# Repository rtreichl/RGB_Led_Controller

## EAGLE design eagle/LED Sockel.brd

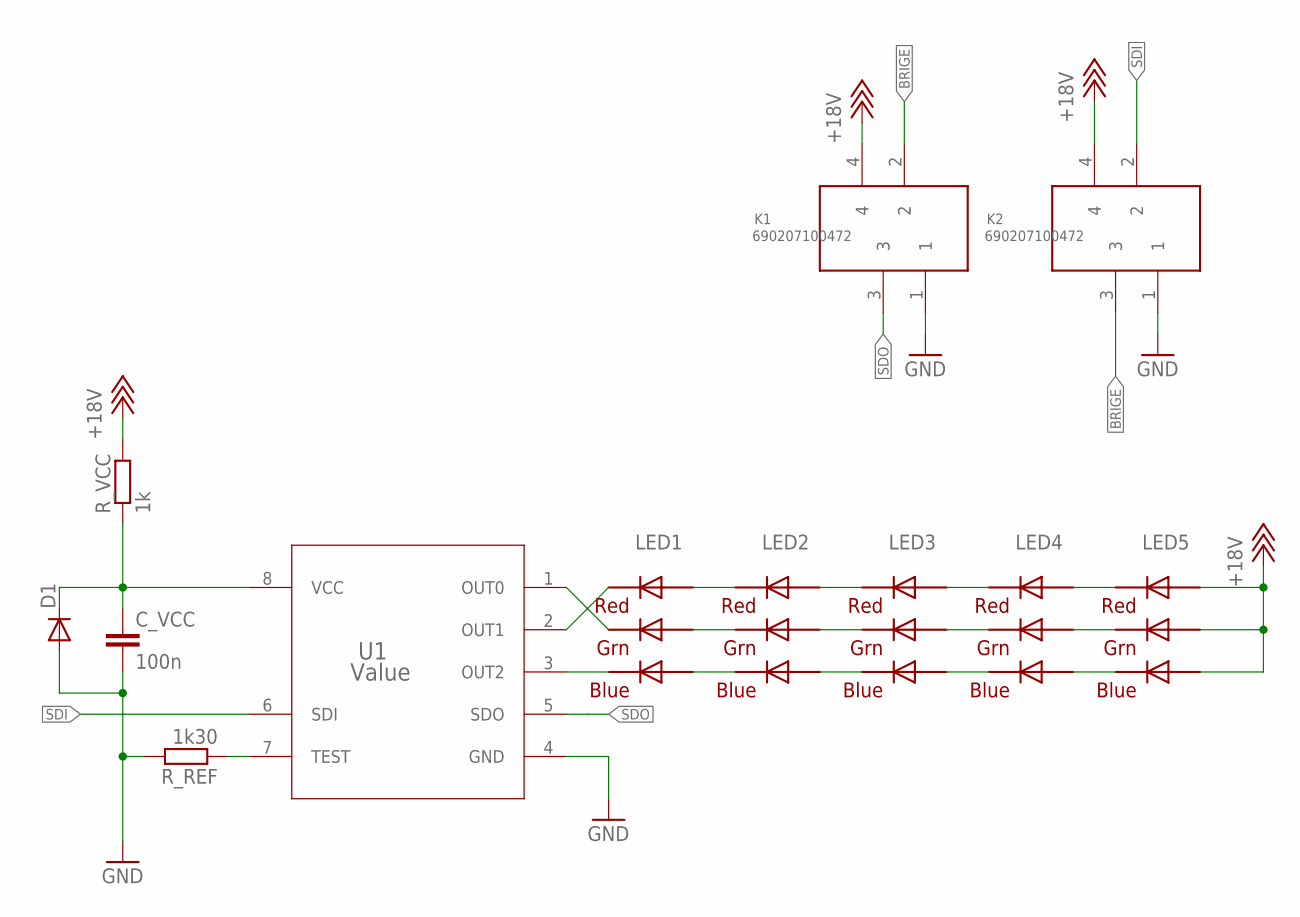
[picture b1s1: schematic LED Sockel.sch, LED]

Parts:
C_VCC: 100n; C0603
D1: DIODE-SOD523; SOD523
K1, K2: 690207100472
LED1, LED2, LED3, LED4, LED5: RGBLED5050
R_REF: 1k30; R0603
R_VCC: 1k; R0805
U1: Value; D0008A_N

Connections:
+18V: K1.4, K2.4, LED5.1 (GREEN_A), LED5.2 (RED_A), LED5.3 (BLUE_A), R_VCC.2
BRIGE: K1.2, K2.3
GND: C_VCC.2, D1.A, K1.1, K2.1, R_REF.2, U1.4 (GND)
unnamed: LED4.1 (GREEN_A), LED5.6 (GREEN_C)
unnamed: LED4.3 (BLUE_A), LED5.4 (BLUE_C)
unnamed: LED4.2 (RED_A), LED5.5 (RED_C)
unnamed: LED3.1 (GREEN_A), LED4.6 (GREEN_C)
unnamed: LED3.3 (BLUE_A), LED4.4 (BLUE_C)
unnamed: LED3.2 (RED_A), LED4.5 (RED_C)
unnamed: LED2.1 (GREEN_A), LED3.6 (GREEN_C)
unnamed: LED2.3 (BLUE_A), LED3.4 (BLUE_C)
unnamed: LED2.2 (RED_A), LED3.5 (RED_C)
unnamed: LED1.1 (GREEN_A), LED2.6 (GREEN_C)
unnamed: LED1.3 (BLUE_A), LED2.4 (BLUE_C)
unnamed: LED1.2 (RED_A), LED2.5 (RED_C)
unnamed: LED1.4 (BLUE_C), U1.3 (OUT2)
unnamed: LED1.6 (GREEN_C), U1.1 (OUT0)
unnamed: LED1.5 (RED_C), U1.2 (OUT1)
unnamed: C_VCC.1, D1.C, R_VCC.1, U1.8 (VCC)
unnamed: R_REF.1, U1.7 (TEST)
SDI: K2.2, U1.6 (SDI)
SDO: K1.3, U1.5 (SDO)

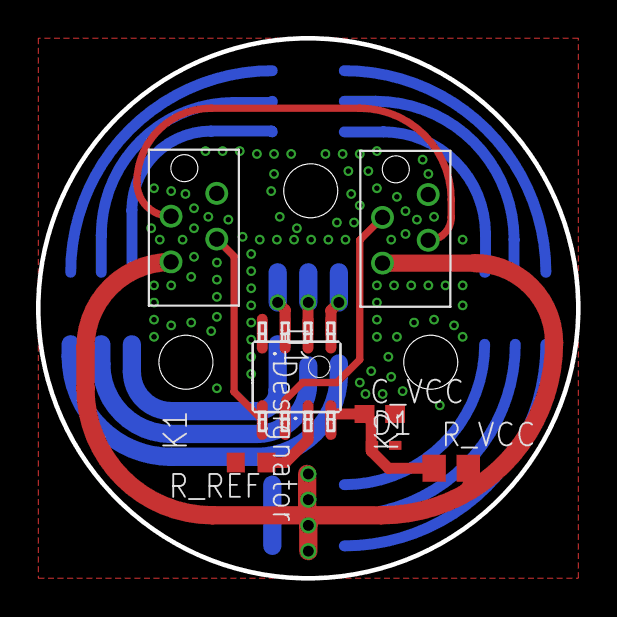
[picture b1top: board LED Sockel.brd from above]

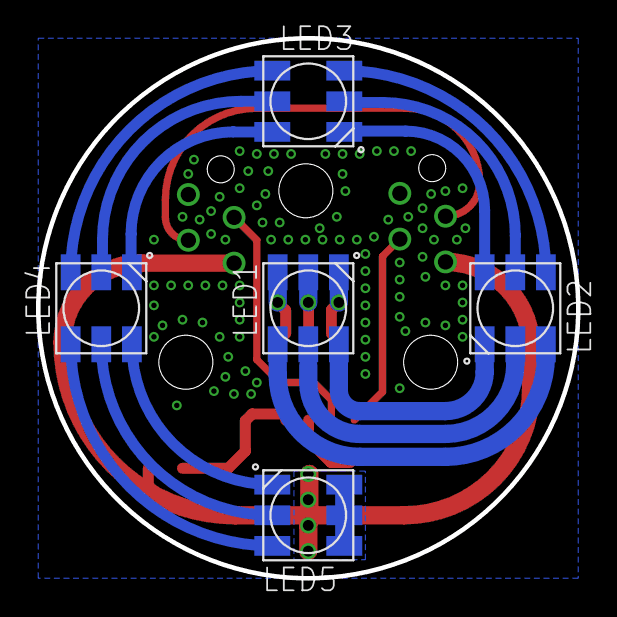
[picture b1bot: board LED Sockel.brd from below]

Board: 2 copper layers, 30.0 x 30.0 mm, 12 parts (5 on the bottom side), 22 nets.

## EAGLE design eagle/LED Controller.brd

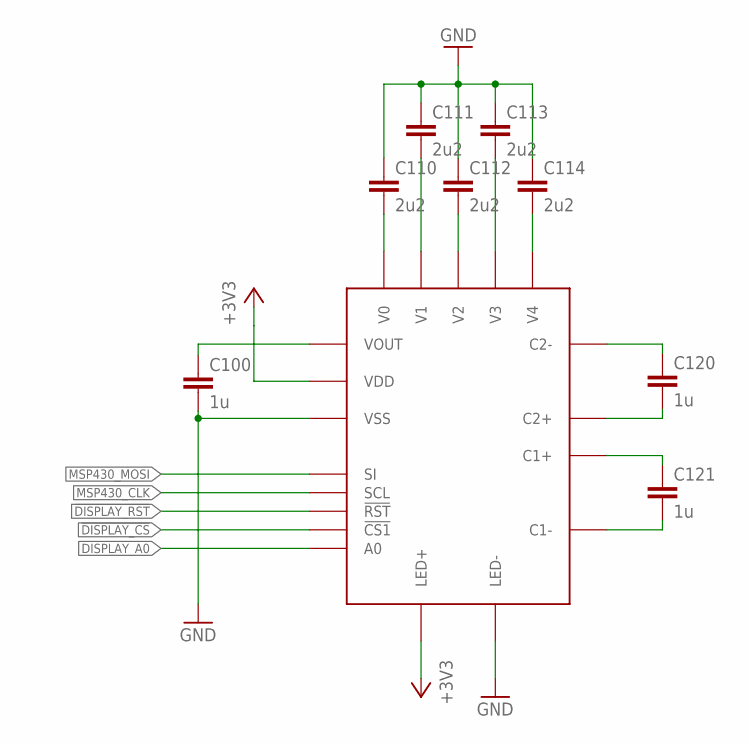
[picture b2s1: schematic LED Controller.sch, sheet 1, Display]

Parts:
C100, C120, C121: 1u; C0603
C110, C111, C112, C113, C114: 2u2; C0603
U$3: DISPLAY; NHD-C12832A1Z-NSW-BBW-3V3

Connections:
!DISPLAY_CS: U$3.P17 (!CS1); also elsewhere on the board
!DISPLAY_RST: U$3.P16 (!RST); also elsewhere on the board
+3V3: U$3.A (LED+), U$3.P12 (VDD); also elsewhere on the board
DISPLAY_A0: U$3.P15 (A0); also elsewhere on the board
GND: C100.2, C110.1, C111.1, C112.1, C113.1, C114.1, U$3.K (LED-), U$3.P11 (VSS); also elsewhere on the board
MSP430_CLK: U$3.P14 (SCL); also elsewhere on the board
MSP430_MOSI: U$3.P13 (SI); also elsewhere on the board
unnamed: C110.2, U$3.P1 (V0)
unnamed: C111.2, U$3.P2 (V1)
unnamed: C112.2, U$3.P3 (V2)
unnamed: C113.2, U$3.P4 (V3)
unnamed: C114.2, U$3.P5 (V4)
unnamed: C120.2, U$3.P7 (C2+)
unnamed: C120.1, U$3.P6 (C2-)
unnamed: C121.1, U$3.P8 (C1+)
unnamed: C121.2, U$3.P9 (C1-)
unnamed: C100.1, U$3.P10 (VOUT)

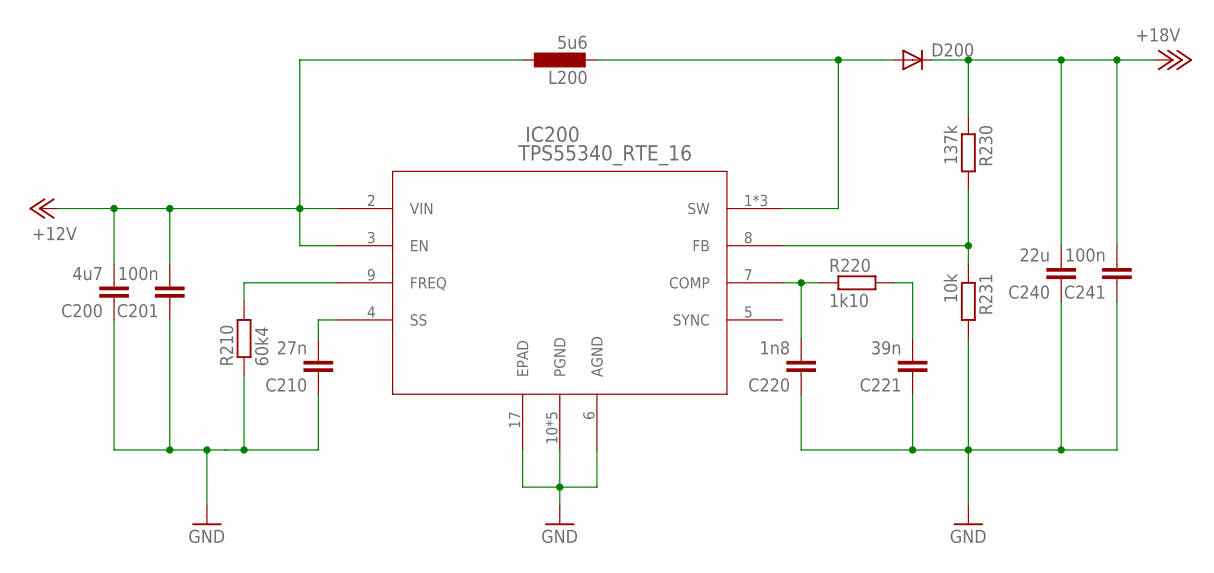
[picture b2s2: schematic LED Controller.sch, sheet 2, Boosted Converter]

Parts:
C200: 4u7; C1206
C201, C241: 100n; C1206
C210: 27n; C0603
C220: 1n8; C0603
C221: 39n; C0603
C240: 22u; C1210
D200: DIODE-SMC; SMC
IC200: TPS55340_RTE_16; RTE16
L200: 5u6; SRP5030T
R210: 60k4; R0603
R220: 1k10; R0603
R230: 137k; R0603
R231: 10k; R0603

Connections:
+12V: C200.2, C201.2, IC200.2 (VIN), IC200.3 (EN), L200.V_1 (1); also elsewhere on the board
+18V: C240.2, C241.2, D200.C, R230.1; also elsewhere on the board
GND: C200.1, C201.1, C210.1, C220.1, C221.1, C240.1, C241.1, IC200.6 (AGND), IC200.10 (PGND), IC200.11 (PGND), IC200.12 (PGND), IC200.13 (PGND), IC200.14 (PGND), IC200.17 (EPAD), R210.1, R231.2; also elsewhere on the board
unnamed: C220.2, IC200.7 (COMP), R220.1
unnamed: D200.A, IC200.1 (SW), IC200.15 (SW), IC200.16 (SW), L200.V_2 (2)
unnamed: IC200.8 (FB), R230.2, R231.1
unnamed: IC200.9 (FREQ), R210.2
unnamed: C210.2, IC200.4 (SS)
unnamed: C221.2, R220.2

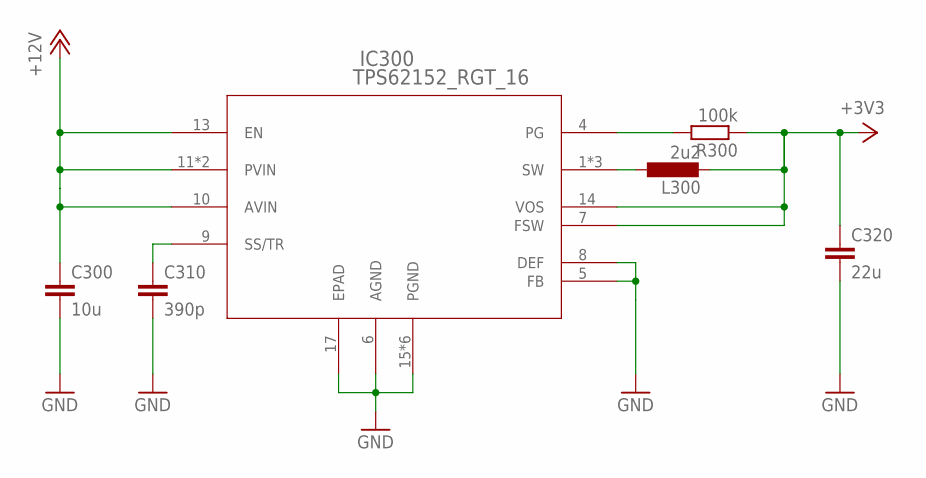
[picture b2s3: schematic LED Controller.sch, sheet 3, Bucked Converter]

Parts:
C300: 10u; C0805
C310: 390p; C0603
C320: 22u; C0805
IC300: TPS62152_RGT_16; RGT16_1P7X1P7
L300: 2u2; SDR0403
R300: 100k; R0603

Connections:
+3V3: C320.1, IC300.7 (FSW), IC300.14 (VOS), L300.V_2 (2), R300.1; also elsewhere on the board
+12V: C300.1, IC300.10 (AVIN), IC300.11 (PVIN), IC300.12 (PVIN), IC300.13 (EN); also elsewhere on the board
GND: C300.2, C310.2, C320.2, IC300.5 (FB), IC300.6 (AGND), IC300.8 (DEF), IC300.15 (PGND), IC300.16 (PGND), IC300.17 (EPAD), IC300.V (PGND), IC300.V_1 (PGND), IC300.V_2 (PGND), IC300.V_3 (PGND); also elsewhere on the board
unnamed: IC300.1 (SW), IC300.2 (SW), IC300.3 (SW), L300.V_1 (1)
unnamed: IC300.4 (PG), R300.2
unnamed: C310.1, IC300.9 (SS/TR)

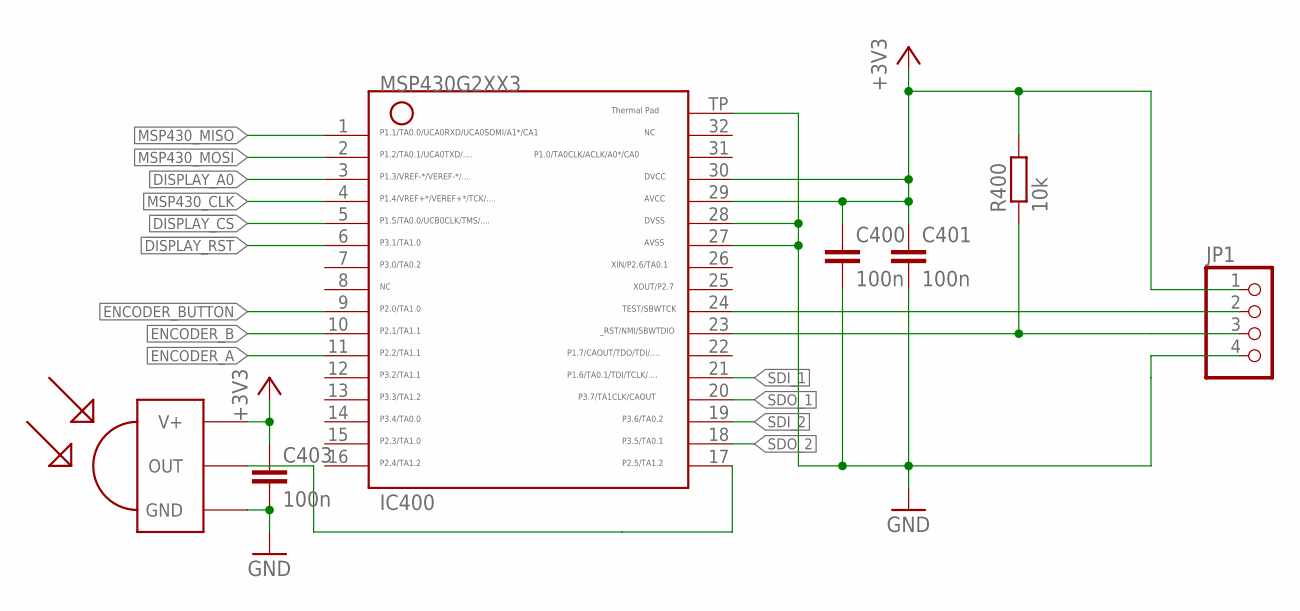
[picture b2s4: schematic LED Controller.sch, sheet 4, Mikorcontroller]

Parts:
C400, C401, C403: 100n; C0603
IC400: G2XX3---RHB32; RHB32
JP1: PINHD-1X4; 1X04
R400: 10k; R0603
U$1: TSOP1738; TSOP17XX

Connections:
!DISPLAY_CS: IC400.5; also elsewhere on the board
!DISPLAY_RST: IC400.6; also elsewhere on the board
+3V3: C400.1, C401.1, C403.1, IC400.29, IC400.30, JP1.1, R400.2, U$1.V+; also elsewhere on the board
DISPLAY_A0: IC400.3; also elsewhere on the board
ENCODER_A: IC400.11; also elsewhere on the board
ENCODER_B: IC400.10; also elsewhere on the board
ENCODER_BUTTON: IC400.9; also elsewhere on the board
GND: C400.2, C401.2, C403.2, IC400.27, IC400.28, IC400.TP, JP1.4, U$1.GND; also elsewhere on the board
MSP430_CLK: IC400.4; also elsewhere on the board
MSP430_MISO: IC400.1
MSP430_MOSI: IC400.2; also elsewhere on the board
unnamed: IC400.24, JP1.2
unnamed: IC400.23, JP1.3, R400.1
unnamed: IC400.17, U$1.OUT
SDI_1: IC400.21; also elsewhere on the board
SDI_2: IC400.19; also elsewhere on the board
SDO_1: IC400.20; also elsewhere on the board
SDO_2: IC400.18; also elsewhere on the board

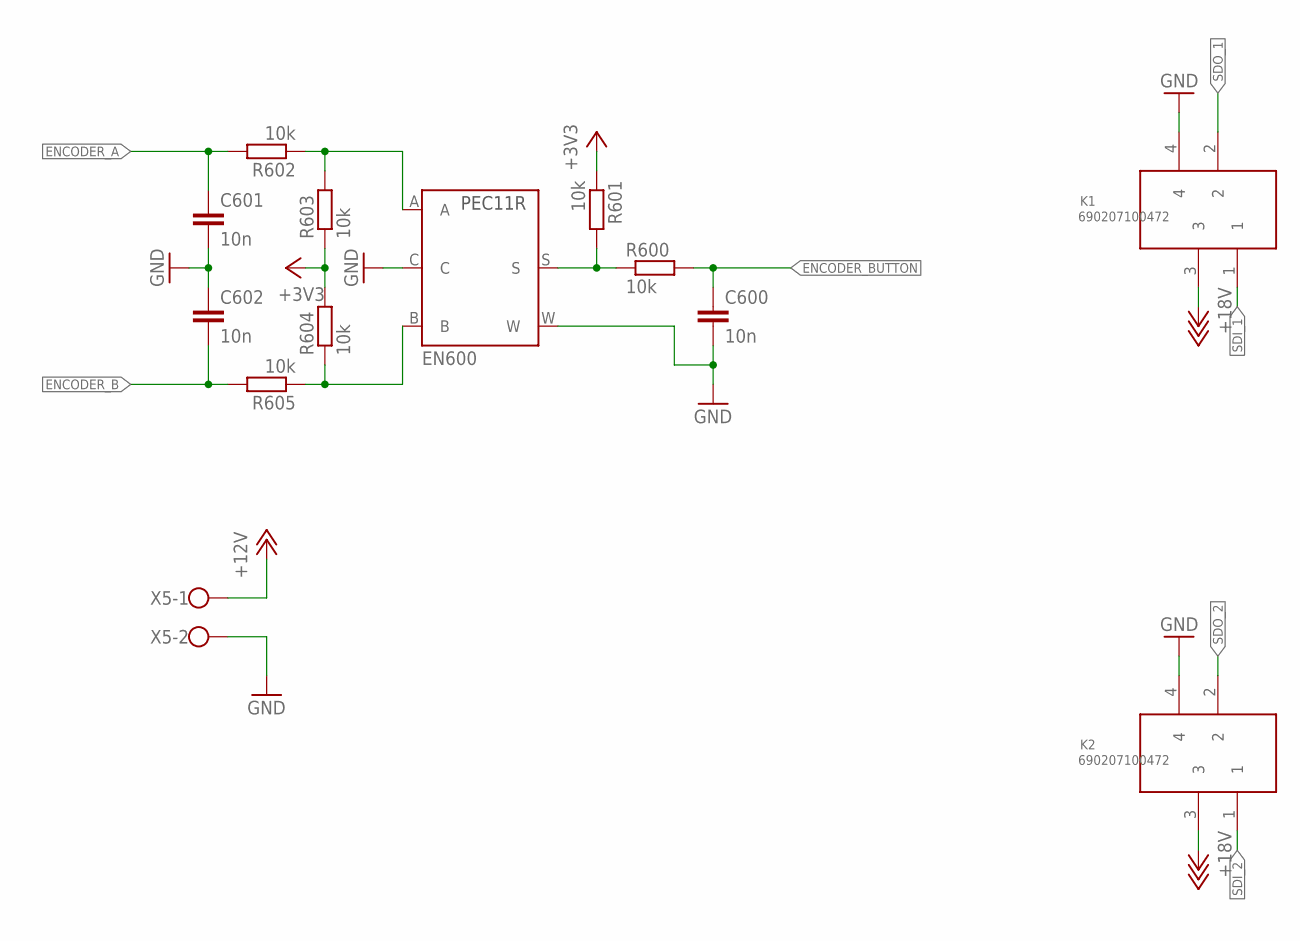
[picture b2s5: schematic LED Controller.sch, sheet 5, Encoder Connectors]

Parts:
C600, C601, C602: 10n; C0603
EN600: PEC11R
K1, K2: 690207100472
R600, R601, R602, R603, R604, R605: 10k; R0603
X5: W237-102

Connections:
+3V3: R601.1, R603.1, R604.2; also elsewhere on the board
+12V: X5.1; also elsewhere on the board
+18V: K1.3, K2.3; also elsewhere on the board
ENCODER_A: C601.1, R602.2; also elsewhere on the board
ENCODER_B: C602.2, R605.2; also elsewhere on the board
ENCODER_BUTTON: C600.1, R600.2; also elsewhere on the board
GND: C600.2, C601.2, C602.1, EN600.C, EN600.W, K1.4, K2.4, X5.2; also elsewhere on the board
unnamed: EN600.A, R602.1, R603.2
unnamed: EN600.B, R604.1, R605.1
unnamed: EN600.S, R600.1, R601.2
SDI_1: K1.1; also elsewhere on the board
SDI_2: K2.1; also elsewhere on the board
SDO_1: K1.2; also elsewhere on the board
SDO_2: K2.2; also elsewhere on the board

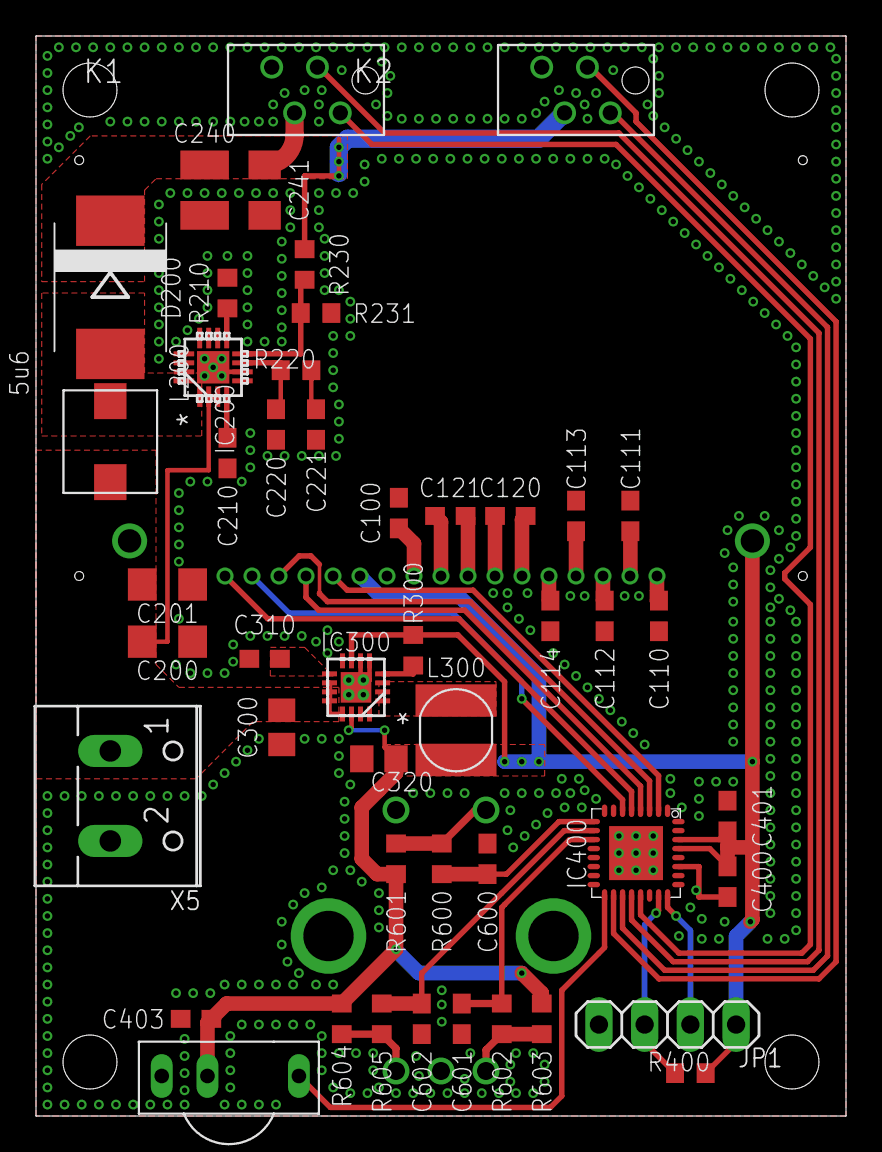
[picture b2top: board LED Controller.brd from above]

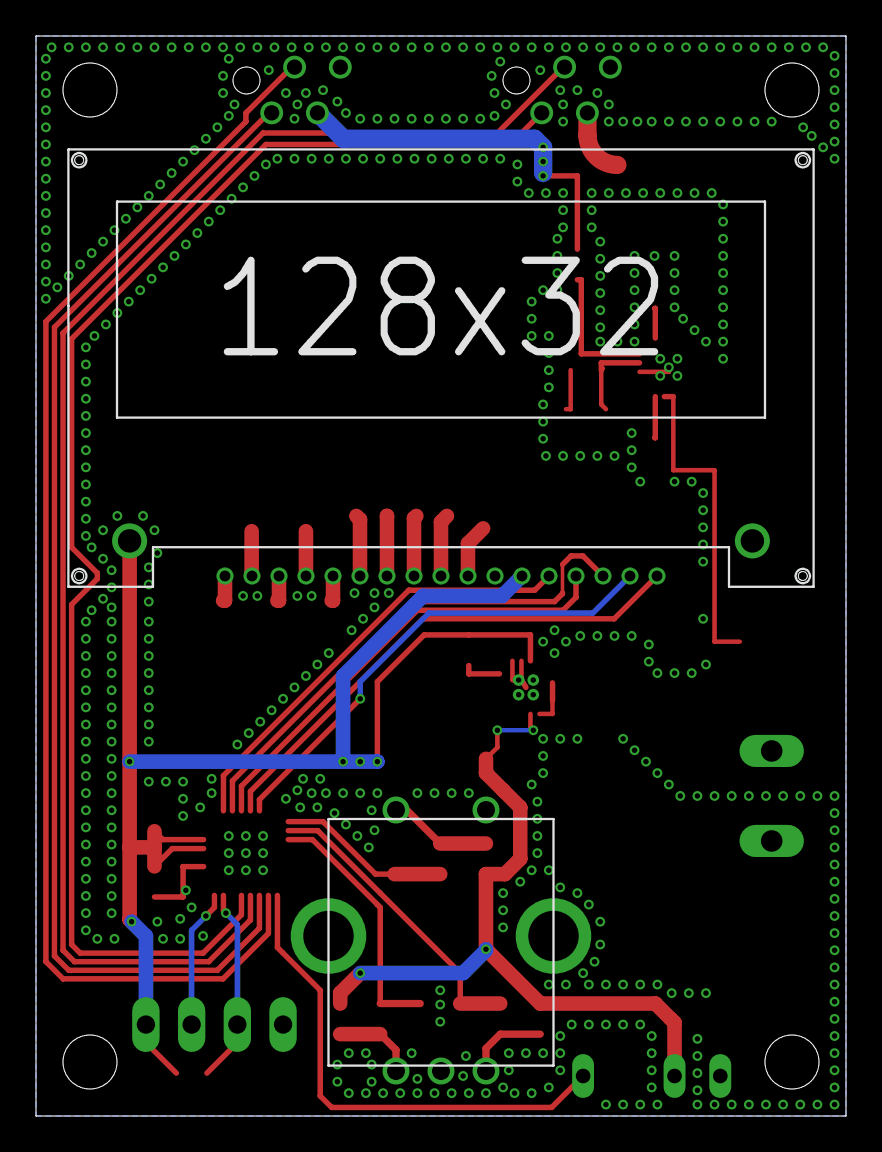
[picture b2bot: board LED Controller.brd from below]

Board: 2 copper layers, 45.0 x 60.0 mm, 49 parts (2 on the bottom side), 41 nets.

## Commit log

2016-02-29 :octocat: Added .gitattributes & .gitignore files
2016-02-29 INIT: Created Projecet

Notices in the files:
parts and their libraries:
Wurth_Elektronik_Electromechanic_Wire_to: Copyright: Würth Elektronik
